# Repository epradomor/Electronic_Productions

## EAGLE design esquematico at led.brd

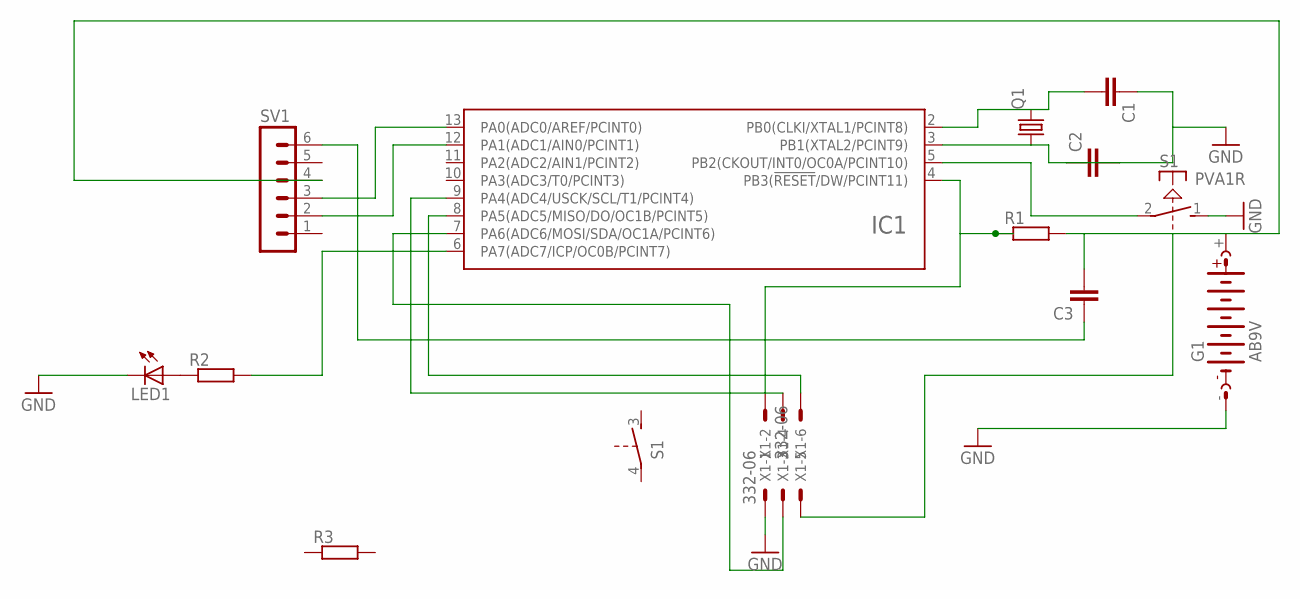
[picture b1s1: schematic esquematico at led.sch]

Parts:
C1, C2, C3: CC1206; C1206
G1: AB9V
IC1: ATTINY24/44/84-SSU; SOIC14
LED1: LED_E; LED_1206
Q1: CRYSTALHC18U-V; HC18U-V
R1, R2, R3: BVS
S1: PVA1R
SV1: MA06-1
X1: 332-06

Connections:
GND: C1.1, C2.1, C2.2, G1.-, IC1.3 (PB1(XTAL2/PCINT9)), IC1.14 (GND), LED1.C, Q1.1, S1.1 (S), X1.1
unnamed: C1.2, IC1.2 (PB0(CLKI/XTAL1/PCINT8)), Q1.2
unnamed: IC1.13 (PA0(ADC0/AREF/PCINT0)), SV1.3
unnamed: IC1.12 (PA1(ADC1/AIN0/PCINT1)), SV1.2
unnamed: IC1.4 (PB3(!RESET!/DW/PCINT11)), R1.2, X1.2
unnamed: IC1.9 (PA4(ADC4/USCK/SCL/T1/PCINT4)), X1.4
unnamed: IC1.8 (PA5(ADC5/MISO/DO/OC1B/PCINT5)), X1.6
unnamed: C3.2, G1.+, R1.1, X1.5
unnamed: IC1.7 (PA6(ADC6/MOSI/SDA/OC1A/PCINT6)), X1.3
unnamed: C3.1, SV1.6
unnamed: IC1.5 (PB2(CKOUT/INT0/OC0A/PCINT10)), S1.2
unnamed: IC1.6 (PA7(ADC7/ICP/OC0B/PCINT7)), R2.1
unnamed: LED1.A, R2.2
UCC: IC1.1 (UCC)

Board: 2 copper layers, 13 parts (0 on the bottom side), 13 nets, no tracks yet.
